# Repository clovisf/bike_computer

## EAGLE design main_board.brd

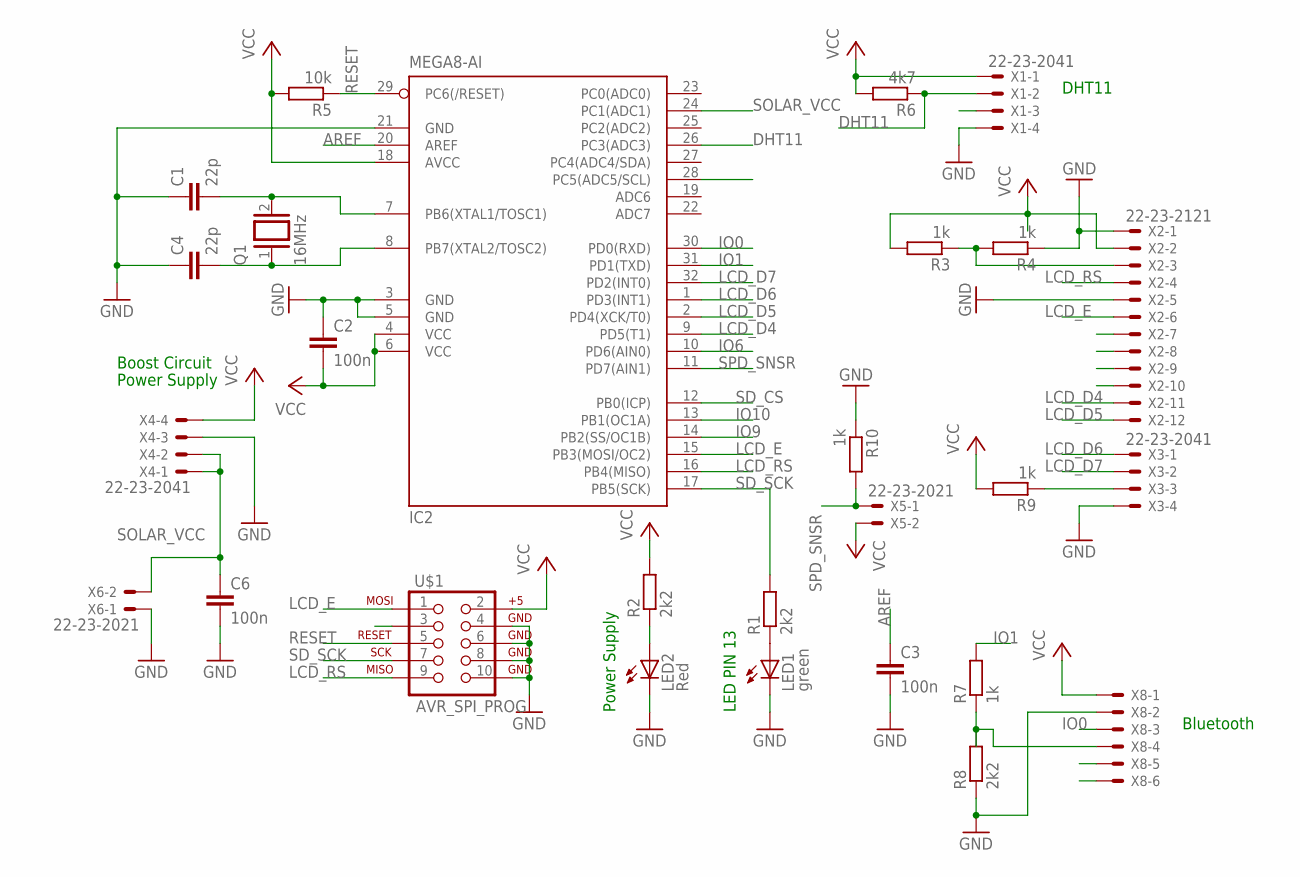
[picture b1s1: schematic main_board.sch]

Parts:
C1, C4: 22p; C2.5-3
C2, C3: 100n; C5B3
C6: 100n; C7.5B6
IC2: MEGA8-AI; TQFP32-08
LED1: green; LED3MM
LED2: Red; LED3MM
Q1: 16MHz; QS
R1, R2, R8: 2k2; 0204V
R3, R4, R7, R9, R10: 1k; 0204V
R5: 10k; 0204V
R6: 4k7; 0204V
U$1: AVR_SPI_PROG; AVR_ICSP
X1, X3, X4: 22-23-2041
X2: 22-23-2121
X5, X6: 22-23-2021
X8: 22-23-2061

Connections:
AREF: C3.1, IC2.20 (AREF)
BMP180_SCL: IC2.28 (PC5(ADC5/SCL))
DHT11: IC2.26 (PC3(ADC3)), R6.1, X1.2
GND: C1.1, C2.1, C3.2, C4.1, C6.2, IC2.3 (GND), IC2.5 (GND), IC2.21 (GND), LED1.K (C), LED2.K (C), R4.1, R8.1, R10.1, U$1.4, U$1.6, U$1.8, U$1.10, X1.4, X2.1, X2.5, X3.4, X4.3, X6.1, X8.2
IO0: IC2.30 (PD0(RXD)), X8.3
IO1: IC2.31 (PD1(TXD)), R7.2
IO6: IC2.10 (PD6(AIN0))
IO9: IC2.14 (PB2(SS/OC1B))
IO10: IC2.13 (PB1(OC1A))
LCD_D4: IC2.9 (PD5(T1)), X2.11
LCD_D5: IC2.2 (PD4(XCK/T0)), X2.12
LCD_D6: IC2.1 (PD3(INT1)), X3.1
LCD_D7: IC2.32 (PD2(INT0)), X3.2
LCD_E: IC2.15 (PB3(MOSI/OC2)), U$1.1, X2.6
LCD_RS: IC2.16 (PB4(MISO)), U$1.9, X2.4
unnamed: C1.2, IC2.7 (PB6(XTAL1/TOSC1)), Q1.2
unnamed: C4.2, IC2.8 (PB7(XTAL2/TOSC2)), Q1.1
unnamed: LED1.A, R1.1
unnamed: LED2.A, R2.1
unnamed: R9.1, X3.3
unnamed: R3.1, R4.2, X2.3
unnamed: R7.1, R8.2, X8.4
RESET: IC2.29 (PC6(/RESET)), R5.1, U$1.5
SD_CS: IC2.12 (PB0(ICP))
SD_SCK: IC2.17 (PB5(SCK)), R1.2, U$1.7
SOLAR_VCC: C6.1, IC2.24 (PC1(ADC1)), X4.1, X4.2, X6.2
SPD_SNSR: IC2.11 (PD7(AIN1)), R10.2, X5.1
VCC: C2.2, IC2.4 (VCC), IC2.6 (VCC), IC2.18 (AVCC), R2.2, R3.2, R5.2, R6.2, R9.2, U$1.2, X1.1, X2.2, X4.4, X5.2, X8.1

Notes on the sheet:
DHT11
LED PIN 13
Power Supply
Boost Circuit
Bluetooth

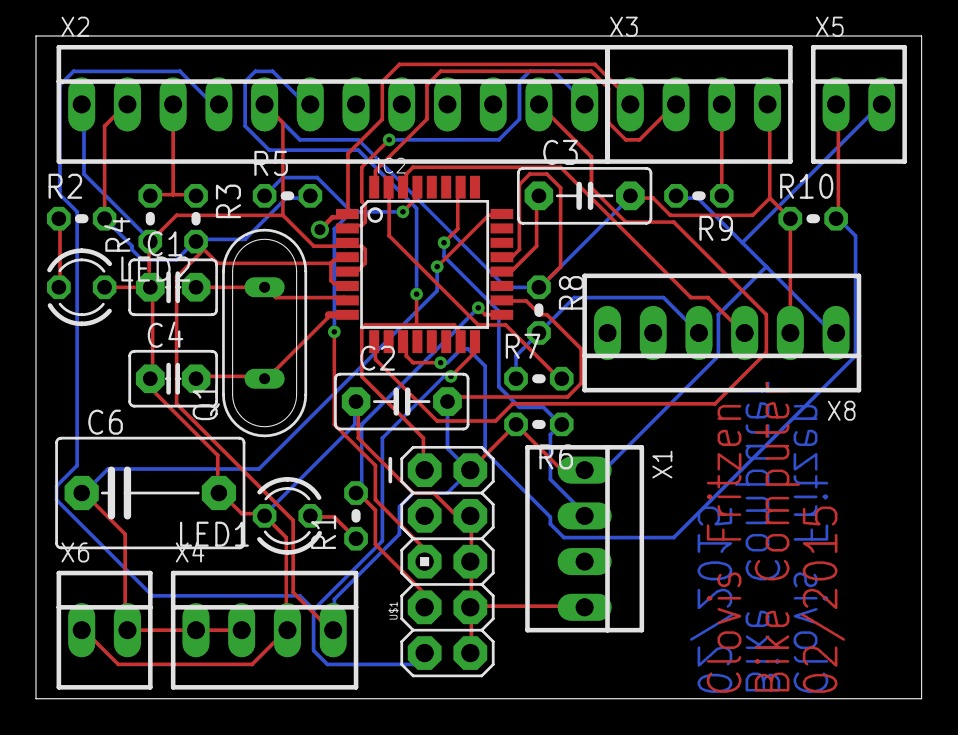
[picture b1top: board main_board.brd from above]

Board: 2 copper layers, 49.2 x 36.8 mm, 27 parts (0 on the bottom side), 23 nets.

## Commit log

2015-02-11 initial release of my bike computer
    An Arduino-based bike computer (odometer), featuring a push-button input
    (for the wheel spin sensor) and a 16x2 LCD for showing data.
2015-04-24 Added temperature sensor, corrected bugs
    Added a DHT11 temperature/humidity sensor to the circuit, showing its values on the LCD screen. Added a home/welcome screen to the LCD, to be played once every power-up. Corrected a major bug that ac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
2015-05-05 added schematics and PCB
    I have added schematic and PCB (Eagle 7.2) files
2017-07-02 changed files path in computer
2017-07-02 added code from third-party

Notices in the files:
parts and their libraries:
SparkFun-Connectors: Licensing: Creative Commons ShareAlike 4.0 International - https://creativecommons.org/licenses/by-sa/4.0
